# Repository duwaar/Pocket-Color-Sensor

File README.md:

### To Do
- Get 8-bit color value from frequency + color selection
- Print RGB hex code
- Match hex code to closest named color
- Design enclosure
- Move OLED screen
- Maybe add LEDs for sanity check
- 

### Lessons Learned
- Solder big components LAST
- Can't desolder SOIC-8 with an iron--hot air rework station necessary
-

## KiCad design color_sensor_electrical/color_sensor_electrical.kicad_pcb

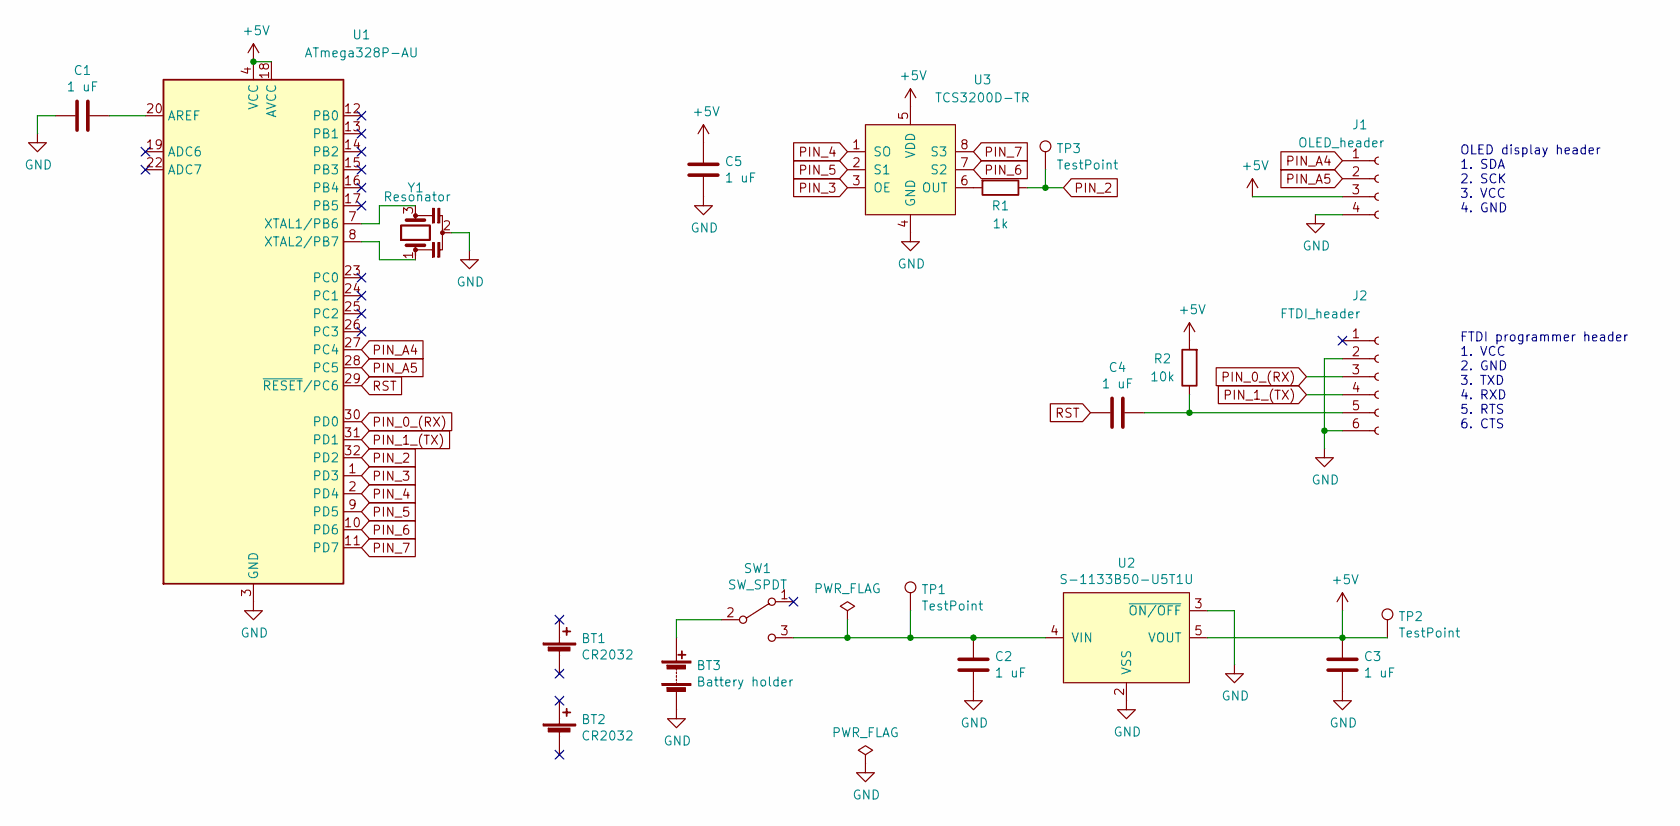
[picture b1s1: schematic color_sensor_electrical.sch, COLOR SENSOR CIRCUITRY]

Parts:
BT1, BT2: CR2032
BT3: Battery holder; Battery_holder_2xCR2032_smd
C1, C2, C3, C4, C5: 1 uF; C_0805_2012Metric
J1: OLED_header; PinSocket_1x04_P2.54mm_Vertical
J2: FTDI_header; PinSocket_1x06_P2.54mm_Vertical
R1: 1k; R_0805_2012Metric
R2: 10k; R_0805_2012Metric
SW1: SW_SPDT; Switch_1825232-1_SPDT
TP1, TP2, TP3: TestPoint; Pin_D1.0mm_L10.0mm
U1: ATmega328P-AU; TQFP-32_7x7mm_P0.8mm
U2: S-1133B50-U5T1U; SOT-89-5_Handsoldering
U3: TCS3200D-TR; SOIC-8_3.9x4.9mm_P1.27mm
Y1: Resonator; Resonator_CSTNE20M0V530000R0_smd_hand-solder

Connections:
+5V: C3.1, C5.1, J1.3, R2.2, TP2.1, U1.4 (VCC), U1.6 (VCC), U1.18 (AVCC), U2.5 (VOUT), U3.5 (VDD)
GND: BT3.2 (-), C1.2, C2.2, C3.2, C5.2, J1.4, J2.2, J2.6, U1.3 (GND), U1.5 (GND), U1.21 (GND), U2.2 (VSS), U2.3 (~ON/OFF), U3.4 (GND), Y1.2
unnamed: BT3.1 (+), SW1.2 (B)
unnamed: C1.1, U1.20 (AREF)
unnamed: C2.1, SW1.3 (C), TP1.1, U2.4 (VIN)
unnamed: C4.1, J2.5, R2.1
unnamed: R1.2, U3.6 (OUT)
unnamed: U1.7 (XTAL1/PB6), Y1.3
unnamed: U1.8 (XTAL2/PB7), Y1.1
PIN_0_(RX): J2.3, U1.30 (PD0)
PIN_1_(TX): J2.4, U1.31 (PD1)
PIN_2: R1.1, TP3.1, U1.32 (PD2)
PIN_3: U1.1 (PD3), U3.3 (OE)
PIN_4: U1.2 (PD4), U3.1 (SO)
PIN_5: U1.9 (PD5), U3.2 (S1)
PIN_6: U1.10 (PD6), U3.7 (S2)
PIN_7: U1.11 (PD7), U3.8 (S3)
PIN_A4: J1.1, U1.27 (PC4)
PIN_A5: J1.2, U1.28 (PC5)
RST: C4.2, U1.29 (~RESET~/PC6)

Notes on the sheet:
OLED display header 1. SDA 2. SCK 3. VCC 4. GND
FTDI programmer header 1. VCC 2. GND 3. TXD 4. RXD 5. RTS 6. CTS

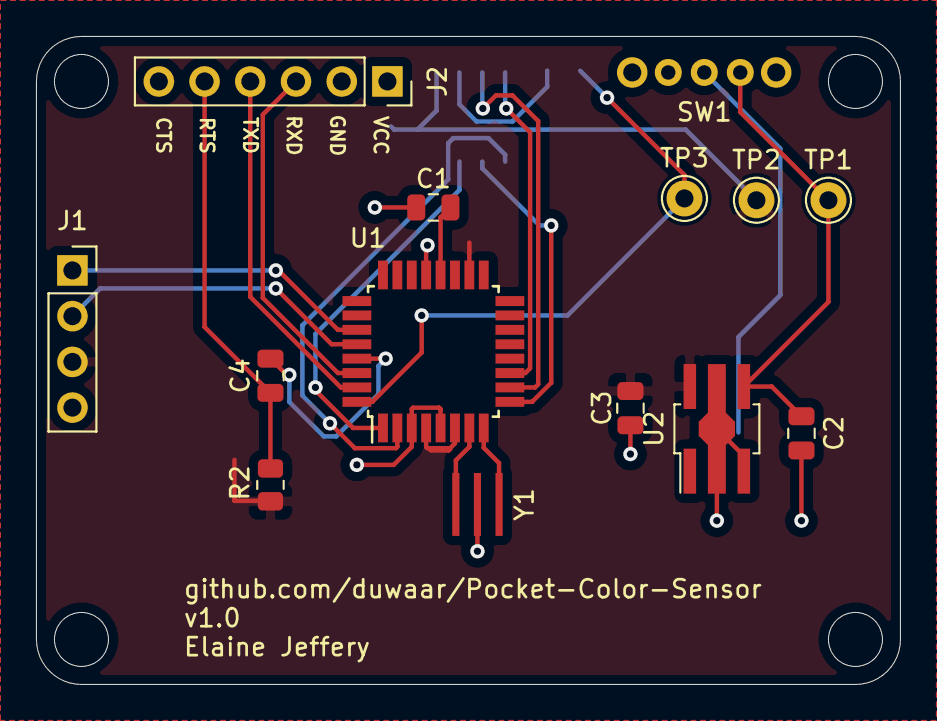
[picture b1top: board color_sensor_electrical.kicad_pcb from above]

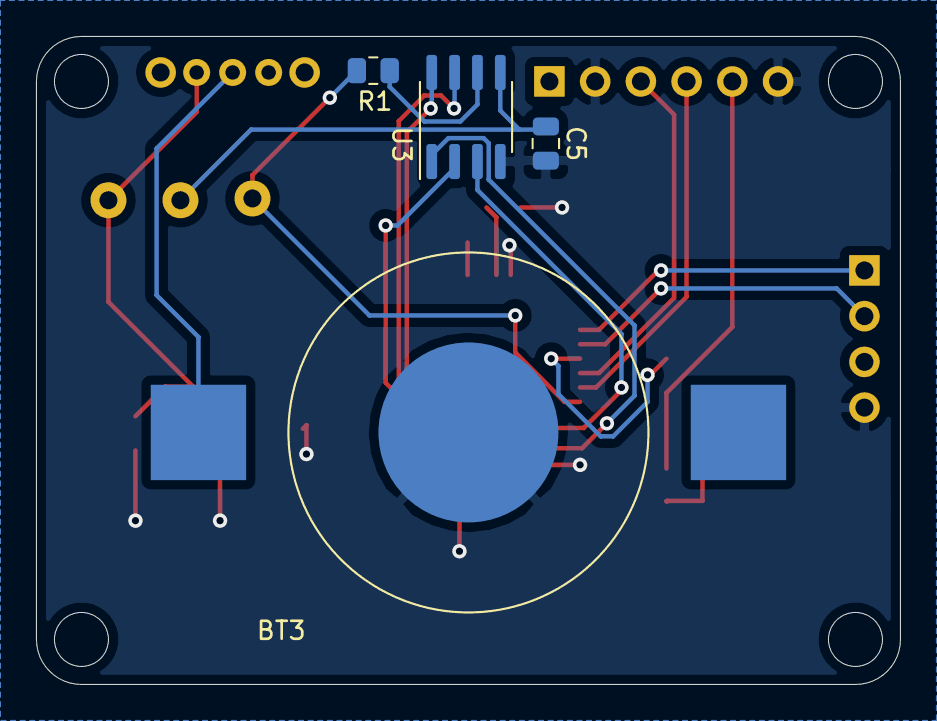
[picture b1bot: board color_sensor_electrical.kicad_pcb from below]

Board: 2 copper layers, 48.0 x 36.0 mm, 18 parts (4 on the bottom side), 20 nets.

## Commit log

2022-07-26 Initial commit.
2022-07-26 Added definitions for TCS3200 class.
2023-02-17 Went back to just Arduino IDE and got it working!
2023-03-05 Changed from .h to .hpp
2023-03-15 Big commit. Changed firmware and made a PCB.
2023-03-22 Almost ready to order board.
2023-04-19 Updated readme after first board assembly.
2023-04-19 Added 3D models to PCB.
